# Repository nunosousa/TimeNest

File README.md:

# TimeNest

**TimeNest** is an open hardware dock that stores and automatically synchronizes radio-controlled solar watches using a locally generated low-frequency time signal.

The device acts as a **watch storage case, time synchronization beacon, and solar charging station**.

Watches placed inside the dock can synchronize reliably even in locations with poor LF radio reception.

---

## Overview

Many radio-controlled watches rely on long-wave radio signals (such as DCF77) to synchronize their time automatically.  
However, indoor reception can often be unreliable due to building structures and interference.

**TimeNest** solves this by generating a **local time signal** synchronized via the internet (SNTP) and transmitting it inside the watch case.

The result is a simple workflow:

1. Place watches inside the case  
2. Close the lid  
3. Watches synchronize automatically

---

## Features

### Radio Time Beacon

- Local generation of radio time signals (DCF77 initially)
- Near-field magnetic antenna
- Adjustable transmission power
- Designed to operate only within the watch case

### Watch Dock

- Storage for multiple watches
- Transparent lid
- Embedded antenna coils inside the case walls
- Elegant desk-friendly design

### Solar Charging

- LED illumination for solar watches
- Configurable brightness
- Optional ambient light sensing
- Illumination scheduling (e.g. daylight simulation)

### Connectivity

- Ethernet time synchronization (SNTP)
- Web configuration interface
- USB serial console for debugging and configuration

### Display

- Current time
- Synchronization status
- Transmission status
- System diagnostics

---

## System Architecture

- RP2040
    - Ethernet MAC + PHY (SPI)
    - lwIP + FreeRTOS
    - SNTP client
    - HTTP configuration server
    - USB serial console
    - DCF77 signal generator
    - external DAC
    - antenna driver
    - LED lighting control
    - display driver

## Platform Choice: RP2040

TimeNest is built around the **RP2040 microcontroller** rather than a microcontroller with an integrated Ethernet MAC. This decision was made deliberately based on several engineering and practical considerations.

### Availability and Supply Stability

One of the primary design goals for TimeNest is long-term reproducibility. During the global semiconductor shortages of 2020–2023 many commonly used MCUs became difficult to source, often with lead times exceeding a year.

The RP2040 demonstrated unusually strong supply stability during that period and remains widely available through multiple distributors. This makes it a reliable choice for a project intended to be reproducible by others in the future.

### Cost Efficiency

The RP2040 is inexpensive compared to many microcontrollers with integrated Ethernet peripherals. Even when combined with an external SPI Ethernet controller, the overall bill of materials remains competitive while retaining design flexibility.

### Strong Ecosystem

The RP2040 has a large and active ecosystem:

- extensive documentation
- a widely used SDK
- strong hobbyist and open hardware community
- support for multiple development environments

This lowers the barrier for contributors and improves long-term maintainability of the project.

### Deterministic Peripherals (PIO)

The RP2040 includes **Programmable I/O (PIO)** peripherals which allow precise timing control independent of the CPU.

This capability is particularly valuable for TimeNest because the device must generate a very stable **low-frequency radio time signal**. Using PIO allows deterministic waveform generation while the main CPU handles networking and other tasks.

### Dual-Core Architecture

The RP2040 provides two CPU cores, which allows the firmware to separate responsibilities:

- one core can handle networking, configuration, and user interface
- the other can manage the timing-critical signal generation tasks

This separation simplifies the firmware architecture and reduces the risk that networking activity interferes with signal timing.

### Flexible Networking Architecture

Although the RP2040 does not include an Ethernet MAC, TimeNest uses an external Ethernet controller connected via SPI.

This approach has several advantages:

- the networking stack remains fully software controlled
- updates and security fixes can be applied through the firmware
- the design avoids reliance on proprietary TCP/IP offload hardware

The project uses a standard embedded TCP/IP stack, making the networking layer maintainable and transparent.

### Simplicity and Accessibility

Another design goal for TimeNest is accessibility for hobbyists and hardware enthusiasts. The RP2040 is widely known and easy to work with, which makes the project easier to reproduce, understand, and modify.

---

### Summary

The RP2040 was chosen because it offers an excellent balance of:

- availability
- cost
- deterministic timing features
- strong community support
- long-term maintainability

While other microcontrollers could provide integrated Ethernet, the RP2040 provides the flexibility and ecosystem that best fit the goals of the TimeNest project.

---

## Why Generate a Local Radio Time Signal?

Many modern watches automatically synchronize their time using long-wave radio transmitters such as **DCF77 (Europe)**, **MSF (UK)**, **WWVB (USA)**, or **JJY (Japan)**.

However, reliable reception of these signals can be difficult indoors due to several factors:

- reinforced concrete buildings
- electrical interference
- distance from transmitters
- geographic coverage limitations

Even within nominal coverage areas, radio-controlled watches often fail to synchronize when placed inside buildings or urban environments.

TimeNest addresses this problem by generating a **local replica of the time signal** synchronized via the internet. The device obtains accurate time using SNTP and then reproduces the radio time signal within the enclosure.

This approach provides several advantages:

- reliable synchronization independent of outdoor reception
- consistent behavior regardless of building environment
- the ability to synchronize multiple watches simultaneously
- predictable synchronization during nightly update windows

By recreating the signal locally, TimeNest effectively acts as a **small personal time beacon** dedicated to the watches placed inside the dock.

---

## Near-Field Magnetic Transmission

TimeNest does not attempt to replicate a full long-range radio transmitter. Instead, it uses **near-field magnetic coupling** to deliver the time signal inside the watch enclosure.

Radio-controlled watches typically contain a **ferrite rod antenna** designed to detect the magnetic field component of long-wave signals. These antennas are very sensitive to nearby magnetic fields even when the radiated electric field is extremely small.

TimeNest takes advantage of this by generating a controlled magnetic field inside the watch case using tuned coils embedded in the enclosure walls.

This design has several benefits:

- extremely low transmission power
- minimal electromagnetic emissions outside the enclosure
- improved reliability for watches placed inside the case
- simplified antenna design

Because the signal only needs to be received within the watch compartment, the system operates entirely in the **near field** rather than attempting long-distance radio transmission.

The result is a compact and efficient system that reliably couples the time signal directly into the watch antennas while keeping the signal confined to the enclosure.

---

## Why Ethernet Instead of Wi-Fi?

TimeNest uses **wired Ethernet** as its network interface instead of Wi-Fi. This was a deliberate design choice based on simplicity, reliability, and the nature of the project.

### Simplicity of Implementation

The primary reason for choosing Ethernet is **system simplicity**.

Supporting Wi-Fi significantly increases firmware and system complexity. A Wi-Fi device must typically implement:

- network discovery and provisioning
- credential storage and management
- connection retry logic
- captive portal or mobile setup workflows
- security updates and maintenance

In contrast, Ethernet provides a **plug-and-play networking experience**:

1. Connect the cable.
2. Obtain an IP address via DHCP.
3. Start synchronizing time.

For a spare-time project, reducing firmware complexity greatly improves development speed and long-term maintainability.

### Reliability

Ethernet also offers **predictable and stable connectivity**. Wired networking avoids common Wi-Fi issues such as:

- RF interference
- signal dropouts
- congestion in the 2.4 GHz band
- router compatibility problems

For a device whose role is to **continuously obtain accurate time from the network**, a stable connection is desirable.

### Timing Considerations

TimeNest synchronizes time over the internet (e.g., via NTP) and generates a **DCF77-compatible time signal**. The required timing accuracy for this application is on the order of **tens of milliseconds**, which both Ethernet and Wi-Fi can easily support.

Therefore, Ethernet was **not chosen for better timing precision**—Wi-Fi would also be sufficient. The decision is instead driven by **simplicity and robustness**.

### Hardware and Firmware Complexity

Adding Wi-Fi would introduce additional hardware and software considerations:

- integration of a radio module
- antenna placement and RF layout constraints
- increased firmware stack complexity
- additional power consumption
- more complex debugging

Using Ethernet allows the device to remain **architecturally simple and deterministic**, which aligns well with the engineering goals of this project.

### Regulatory Considerations

Ethernet-only devices are treated as **unintentional radiators** from an electromagnetic compatibility (EMC) perspective. Adding Wi-Fi would turn the device into an **intentional RF transmitter**, bringing additional regulatory requirements under radio equipment directives.

While this is mainly relevant if the project were ever commercialized, avoiding an integrated radio simplifies the compliance landscape.

### Product Positioning

Many professional time distribution devices—such as **NTP servers and timing appliances**—use wired networking for the same reasons: reliability, determinism, and simplicity.

TimeNest follows this philosophy by favoring a **stable wired network interface** rather than a wireless one.

---

In short, Ethernet was selected because it provides the **simplest, most reliable, and most maintainable networking solution** for the goals of this project.

---

## Design Principles

TimeNest is designed as an open hardware project with an emphasis on simplicity, reproducibility, and responsible radio use. The following principles guide the design decisions throughout the project.

### Reproducibility

A core goal of TimeNest is that the device can be built and modified by others. Component choices and system architecture are selected with long-term availability in mind, and all design files are published in the repository.

The project includes:

- PCB design files
- firmware source code
- enclosure CAD models
- documentation describing design decisions

This allows others to reproduce, study, and extend the device.

### Modularity

TimeNest separates major system responsibilities into independent modules:

- RF signal generation
- networking and time synchronization
- user interface
- enclosure and antenna system

This modular structure simplifies development and makes the system easier to maintain or extend.

### Deterministic Timing

Generating a reliable radio time signal requires stable and predictable timing. The system architecture therefore prioritizes deterministic signal generation and isolates time-critical tasks from networking and user interface functionality.

This ensures that background tasks such as networking or configuration do not interfere with signal generation.

### Minimal RF Emissions

TimeNest is designed to operate entirely within the watch enclosure using near-field magnetic coupling rather than long-range radio transmission.

This approach:

- minimizes radiated emissions
- reduces interference with other devices
- keeps the system focused on synchronizing watches inside the dock

### Transparency

Design decisions are documented whenever possible so that the reasoning behind the system architecture is clear. Open documentation helps contributors understand the project and provides useful reference material for similar designs.

### Practical Simplicity

Where possible, the design favors simple and robust solutions over unnecessary complexity. The goal is a device that is reliable, understandable, and easy to reproduce rather than one that maximizes feature count.

---

## How It Works

TimeNest synchronizes radio-controlled watches by recreating a standard long-wave time signal inside the watch enclosure. The device obtains accurate time from the internet and converts it into a locally generated radio time signal that watches can receive.

The signal path can be summarized as follows:

### Time Synchronization

TimeNest retrieves accurate time using **SNTP (Simple Network Time Protocol)** over Ethernet.  
The device periodically synchronizes with an NTP server and maintains a local system clock.

### Time Signal Encoding

Once the correct time is known, the firmware constructs the **DCF77 time frame**, which encodes:

- current minute
- hour
- date
- day of week
- daylight saving time information
- parity bits

DCF77 transmits one bit per second using amplitude modulation of a 77.5 kHz carrier.

### Carrier Generation

The RF carrier is generated using a **Direct Digital Synthesis (DDS)** approach implemented on the RP2040.  
The DDS produces a stable 77.5 kHz waveform that serves as the carrier for the time signal.

### Modulation

The DCF77 signal encodes bits using brief reductions in carrier amplitude:

- **100 ms reduction** → logical 0  
- **200 ms reduction** → logical 1  

The firmware controls this modulation pattern according to the generated time frame.

### Analog Signal Output

The synthesized waveform is converted to an analog signal using a **digital-to-analog converter (DAC)** and then amplified by a small RF driver stage.

### Magnetic Field Generation

The amplified signal drives **resonant antenna coils embedded in the enclosure walls**. These coils generate a low-frequency magnetic field inside the watch compartment.

Because radio-controlled watches use **ferrite rod antennas**, they can detect this magnetic field even though the transmission power is extremely small.

### Watch Synchronization

Watches placed inside the dock receive the locally generated signal just as they would receive the original DCF77 transmission. During their normal nightly synchronization window, the watches decode the signal and update their internal clocks.

By generating the signal locally, TimeNest ensures reliable synchronization even in environments where the original long-wave broadcast cannot be received.

---

## Hardware

Main components include:

- RP2040 microcontroller
- SPI Ethernet controller
- external DAC for signal generation
- resonant LF antenna coils
- LED lighting system
- small display
- optional RTC

Hardware design files can be found in:

hardware/pcb

---

## Antenna

TimeNest uses **near-field magnetic transmission**.

Two coils embedded in the case walls generate a uniform magnetic field inside the watch compartment, allowing reliable synchronization for all watches inside the box.

---

## Enclosure

The enclosure is a **3D-printed watch case** designed to hold multiple watches.

Features include:

- transparent lid
- integrated antenna coils
- solar charging LEDs
- front status display
- rear connectors (Ethernet, USB, power)

CAD files are located in:

enclosure/cad

---

## Repository Structure

- TimeNest
    - firmware/ RP2040 firmware
    - hardware/ schematics and PCB layout
    - enclosure/ CAD models and STL files
    - docs/ design notes and documentation
    - images/ renders and photos

---

## Roadmap

| Feature | Status |
|-------|--------|
| Project concept | ✅ done |
| System architecture | 🔄 in progress |
| RP2040 platform selection | 🔄 in progress |
| DCF77 signal generator | ⏳ planned |
| DAC output stage | ⏳ planned |
| Antenna design | ⏳ planned |
| Ethernet networking | ⏳ planned |
| SNTP time synchronization | ⏳ planned |
| Web configuration interface | ⏳ planned |
| USB debug interface | ⏳ planned |
| Solar charging LEDs | ⏳ planned |
| Enclosure CAD design | ⏳ planned |
| Multi-protocol support (WWVB / MSF / JJY) | 💡 future idea |

Legend:

⏳ planned

🔄 in progress

✅ done

💡 future idea

---

## Development Log

- 2026-03 — project started
- architecture defined
- antenna concept explored
- enclosure concept designed

More updates will be added as development progresses.

---

## Getting Started

Documentation and assembly instructions will be added as the hardware and firmware mature.

---

## Contributing

Contributions, ideas, and feedback are welcome.

If you are interested in:

- RF design
- embedded firmware
- mechanical design
- watch technology

feel free to open an issue or start a discussion.

---

## Project Status

TimeNest is currently in **early development**.

## Acknowledgements

Some parts of the project documentation and early concept brainstorming were assisted by AI tools.  
All hardware, firmware, and mechanical design decisions are reviewed and implemented by the project author.

## License

TimeNest is an open hardware project.

Different parts of the project are licensed under different licenses:

| Component | License |
|---|---|
Firmware | MIT License |
Hardware (schematics, PCB) | CERN-OHL-S v2 |
Enclosure CAD | CERN-OHL-S v2 |
Documentation and images | CC BY 4.0 |

See the `LICENSES` folder for full license texts.

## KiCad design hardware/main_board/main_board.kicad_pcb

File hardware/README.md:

# Hardware

This directory contains the electronic design files for TimeNest.

## Contents

- schematics
- PCB layout
- component libraries
- manufacturing files

The main PCB includes:

- RP2040 microcontroller
- Ethernet MAC/PHY
- DAC for signal generation
- antenna driver
- LED drivers
- power supply circuitry

## Tools

The PCB is designed using KiCad.

## Status

Hardware design is currently in early development.

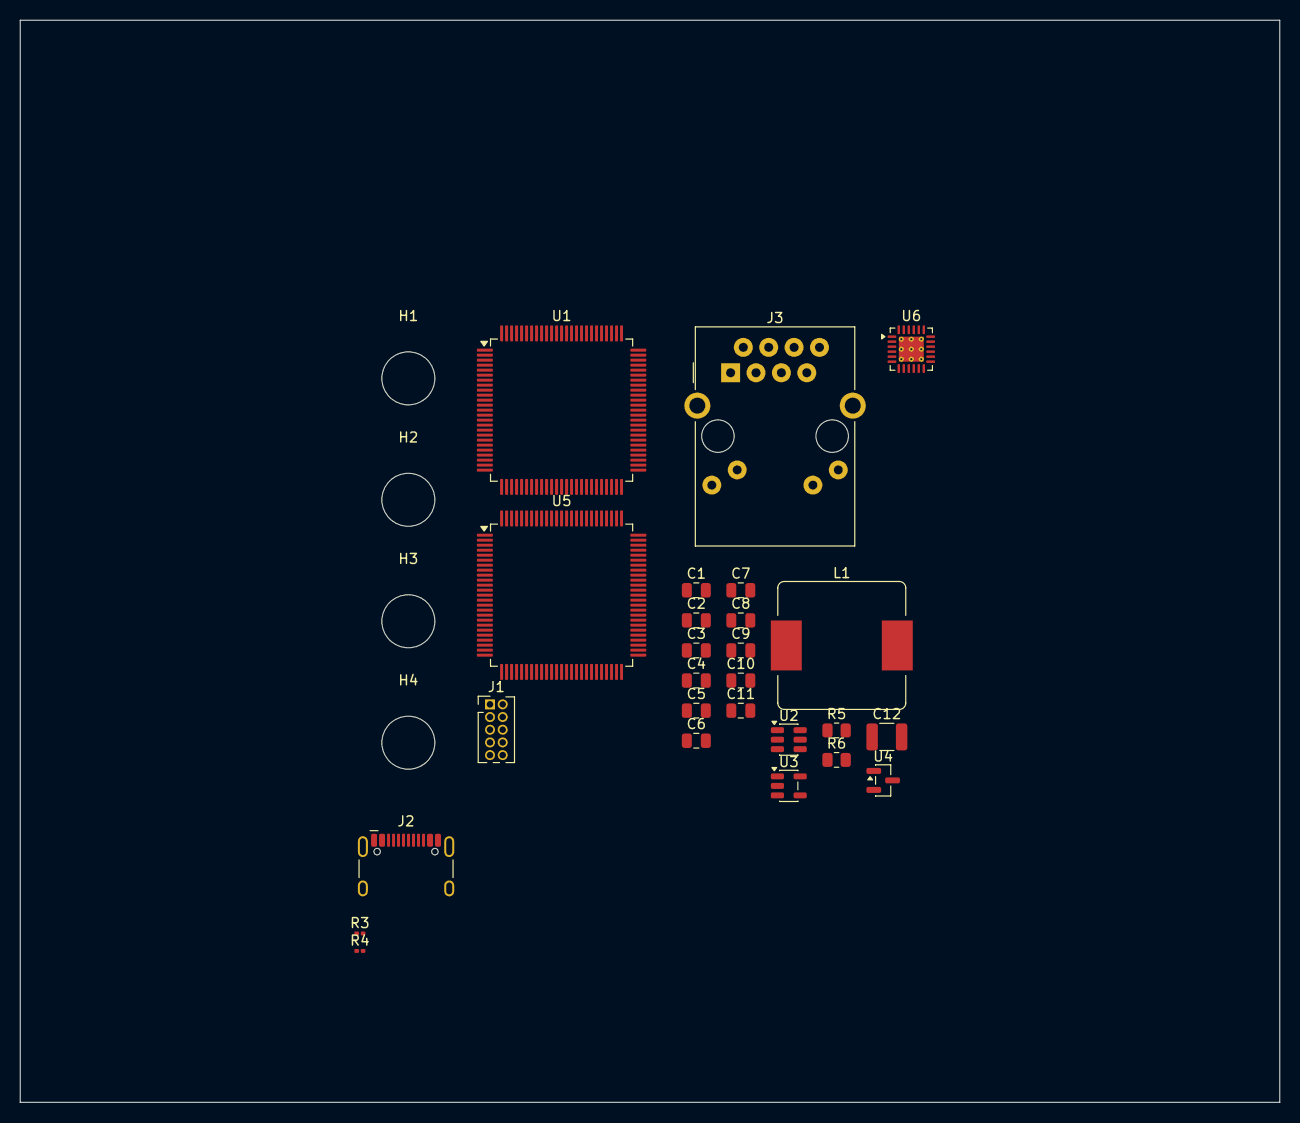
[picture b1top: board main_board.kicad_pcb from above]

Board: 4 copper layers, 126.0 x 108.2 mm, 30 parts (0 on the bottom side), 11 nets, no tracks yet.

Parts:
C1, C3, C4, C8, C9: 100nC; C_0805_2012Metric
C2, C5, C6, C7, C10: 10uC; C_0805_2012Metric
C11: C; C_0805_2012Metric
C12: C; C_1210_3225Metric
H1, H2, H3, H4: MountingHole; MountingHole_5.3mm_M5
J1: Conn_ARM_JTAG_SWD_10; PinHeader_2x05_P1.27mm_Vertical
J2: USB_C_Receptacle_USB2.0_16P; USB_C_Receptacle_HCTL_HC-TYPE-C-16P-01A
J3: RJ45_Amphenol_RJMG1BD3B8K1ANR
L1: L; L_TaiTech_TMPC1265_13.5x12.5mm
R3, R4: 27R; R_0201_0603Metric
R5, R6: R; R_0805_2012Metric
U1: STM32H563VITx; LQFP-100_14x14mm_P0.5mm
U2: TPS54202DDC; SOT-23-6
U3: TLV75533PDBV; SOT-23-5
U4: REF3033; SOT-23
U5: STM32F407VETx; LQFP-100_14x14mm_P0.5mm
U6: LAN8742A; VQFN-24-1EP_4x4mm_P0.5mm_EP2.5x2.5mm_ThermalVias

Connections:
+3.3V: C8.1, C10.1, J1.1 (VTref), U3.5 (OUT)
+12V: C1.1, C2.1, C5.1, U2.3 (VIN), U2.5 (EN)
GND: C1.2, C2.2, C3.2, C4.2, C5.2, C6.2, C7.2, C8.2, C10.2, C12.2, J1.3 (GND), J1.5 (GND), J1.9 (GNDDetect), J2.A1 (GND), J2.A12 (GND), J2.B1 (GND), J2.B12 (GND), J2.SH (SHIELD), R6.2, U2.1 (GND), U3.2 (GND), U4.3 (GND)
unnamed: J2.A6 (D+), J2.B6 (D+), R4.1
unnamed: J2.A7 (D-), J2.B7 (D-), R3.1
unnamed: U1.10 (VSS), U1.27 (VSS), U1.49 (VSS), U1.74 (VSS), U1.99 (VSS)
unnamed: C9.1, U2.6 (BOOT)
unnamed: C11.2, R5.2, R6.1, U2.4 (FB)
unnamed: C9.2, L1.1, U2.2 (SW)
unnamed: C3.1, C4.1, C6.1, C7.1, C11.1, C12.1, L1.2, R5.1, U3.1 (IN), U3.3 (EN), U4.1 (IN)
unnamed: U5.10 (VSS), U5.27 (VSS), U5.74 (VSS), U5.99 (VSS)

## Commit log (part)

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2026-03-15 Updates README with project details
    Expanded the README to provide detailed information about TimeNest, including features, system architecture, hardware components, antenna design, enclosure specifications, repository structure, roadm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
2026-03-15 Update README: add banner, images, status
2026-03-15 Add README docs and license files
2026-03-15 Document RP2040 choice and add architecture SVG
2026-03-24 Created new PCB project.
2026-06-15 Progressed ECAD.
